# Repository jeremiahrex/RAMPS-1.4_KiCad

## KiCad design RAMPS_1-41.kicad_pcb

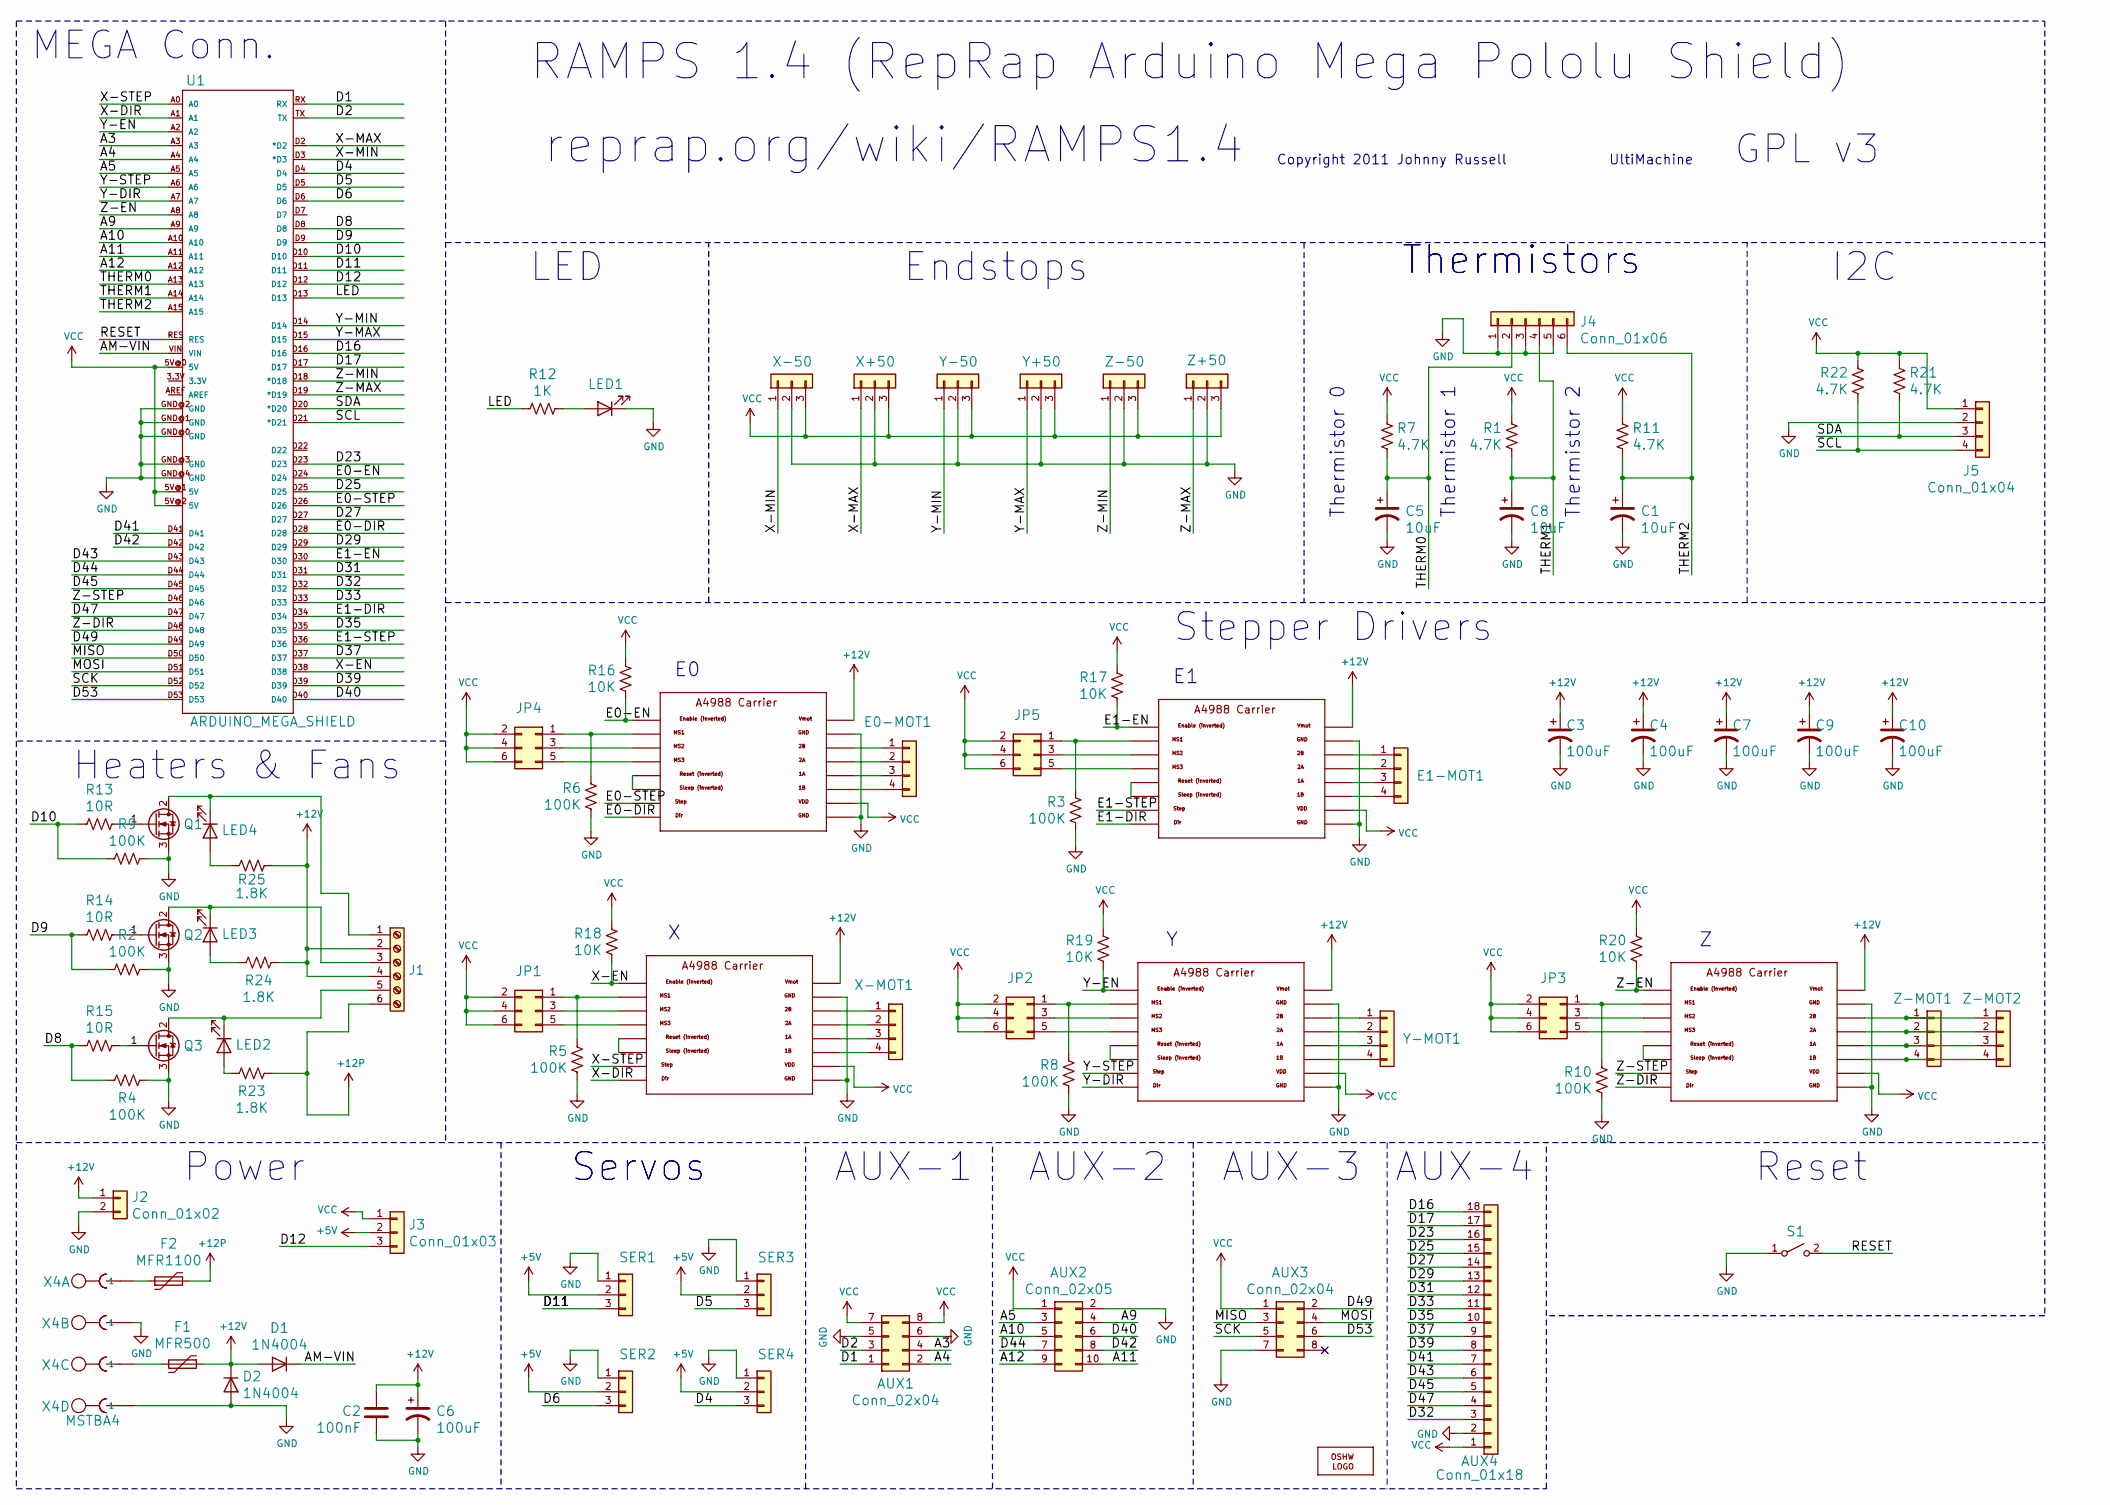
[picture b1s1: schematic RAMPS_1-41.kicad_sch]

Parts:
AUX1, AUX3: Conn_02x04; PIN-HEADER-2x04
AUX2: Conn_02x05; PIN-HEADER-2x05
AUX4: Conn_01x18; PIN-HEADER-1x18
C1, C5, C8: 10uF; CP_Elec_4x5.3
C2: 100nF; C_0805_2012Metric
C3, C4, C6, C7, C9, C10: 100uF; CP_Elec_6.3x5.4
D1, D2: 1N4004; D_DO-41_SOD81_P10.16mm_Horizontal
E0-MOT1, E1-MOT1: PIN-HEADER-1x04
F1: MFR500
F2: MFR1100
J1: 282837-6; TerminalBlock_MetzConnect_Type101_RT01606HBWC_1x06_P5.08mm_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
J2: Conn_01x02; PIN-HEADER-1x02
J3: Conn_01x03; PIN-HEADER-1x03
J4: Conn_01x06; PIN-HEADER-1x06
J5: Conn_01x04; PIN-HEADER-1x04
JP1, JP2, JP3, JP4, JP5: PIN-HEADER-2x03
LED1, LED2, LED3, LED4: LED_0805
LOGO1: OSHW_LOGO_6MILX0100-NT; OSHW_OSHW_6X100_NOTEXT
Q1, Q2, Q3: STP55NF06L; TRANSISTOR-POWER_TO220BV
R1, R7, R11, R21, R22: 4.7K; R_0805_2012Metric
R2, R3, R4, R5, R6, R8, R9, R10: 100K; R_0805_2012Metric
R12: 1K; R_0805_2012Metric
R13, R14, R15: 10R; R_0805_2012Metric
R16, R17, R18, R19, R20: 10K; R_0805_2012Metric
R23, R24, R25: 1.8K; R_0805_2012Metric
S1: SWITCH-OMRON_B3F-31XX
SER1, SER2, SER3, SER4: Conn_01x03; PIN-HEADER-1x03
U1: ARDUINO_MEGA_SHIELD
U2, U3, U4, U5, U6: A4988BREAKOUT; A4988_BREAKOUT
X4: MSTBA4; PhoenixContact_MSTBA_2,5_4-G-5,08_1x04_P5.08mm_Horizontal
X+50: PIN-HEADER-1x03
X-50: PIN-HEADER-1x03
X-MOT1: PIN-HEADER-1x04
Y+50: PIN-HEADER-1x03
Y-50: PIN-HEADER-1x03
Y-MOT1: PIN-HEADER-1x04
Z+50: PIN-HEADER-1x03
Z-50: PIN-HEADER-1x03
Z-MOT1, Z-MOT2: PIN-HEADER-1x04

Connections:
+5V: J3.2, SER1.2, SER2.2, SER3.2, SER4.2
+12P: F2.2, J1.6, R23.2
+12V: C2.1, C3.1, C4.1, C6.1, C7.1, C9.1, C10.1, D1.2 (A), D2.1 (K), F1.1, J1.2, J1.4, J2.1, R24.2, R25.2, U2.VMOT, U3.VMOT, U4.VMOT, U5.VMOT, U6.VMOT
/A3: AUX1.4, U1.A3
/A4: AUX1.2, U1.A4
/A5: AUX2.3, U1.A5
/A9: AUX2.4, U1.A9
/A10: AUX2.5, U1.A10
/A11: AUX2.10, U1.A11
/A12: AUX2.9, U1.A12
/AM-VIN: D1.1 (K), U1.VIN
/D1: AUX1.1, U1.RX
/D2: AUX1.3, U1.TX
/D4: SER4.3, U1.D4
/D5: SER3.3, U1.D5
/D6: SER2.3, U1.D6
/D8: R4.2, R15.2, U1.D8
/D9: R2.2, R14.2, U1.D9
/D10: R9.2, R13.2, U1.D10
/D11: SER1.3, U1.D11
/D12: J3.3, U1.D12
/D16: AUX4.18, U1.D16
/D17: AUX4.17, U1.D17
/D23: AUX4.16, U1.D23
/D25: AUX4.15, U1.D25
/D27: AUX4.14, U1.D27
/D29: AUX4.13, U1.D29
/D31: AUX4.12, U1.D31
/D32: AUX4.3, U1.D32
/D33: AUX4.11, U1.D33
/D35: AUX4.10, U1.D35
/D37: AUX4.9, U1.D37
/D39: AUX4.8, U1.D39
/D40: AUX2.6, U1.D40
/D41: AUX4.7, U1.D41
/D42: AUX2.8, U1.D42
/D43: AUX4.6, U1.D43
/D44: AUX2.7, U1.D44
/D45: AUX4.5, U1.D45
/D47: AUX4.4, U1.D47
/D49: AUX3.2, U1.D49
/D53: AUX3.6, U1.D53
/E0-DIR: U1.D28, U5.DIR
/E0-EN: R16.1, U1.D24, U5.EN
/E0-STEP: U1.D26, U5.STEP
/E1-DIR: U1.D34, U6.DIR
/E1-EN: R17.1, U1.D30, U6.EN
/E1-STEP: U1.D36, U6.STEP
/LED: R12.1, U1.D13
/MISO: AUX3.3, U1.D50
/MOSI: AUX3.4, U1.D51
/RESET: S1.2 (B), U1.RES
/SCK: AUX3.5, U1.D52
/SCL: J5.4, R22.2, U1.D21 (*D21)
/SDA: J5.3, R21.2, U1.D20 (*D20)
/THERM0: C5.1, J4.2, R7.2, U1.A13
/THERM1: C8.1, J4.4, R1.2, U1.A14
/THERM2: C1.1, J4.6, R11.2, U1.A15
/X-DIR: U1.A1, U2.DIR
/X-EN: R18.1, U1.D38, U2.EN
/X-MAX: U1.D2 (*D2), X+50.1
/X-MIN: U1.D3 (*D3), X-50.1
/X-STEP: U1.A0, U2.STEP
/Y-DIR: U1.A7, U3.DIR
/Y-EN: R19.1, U1.A2, U3.EN
/Y-MAX: U1.D15, Y+50.1
/Y-MIN: U1.D14, Y-50.1
/Y-STEP: U1.A6, U3.STEP
/Z-DIR: U1.D48, U4.DIR
/Z-EN: R20.1, U1.A8, U4.EN
/Z-MAX: U1.D19 (*D19), Z+50.1
/Z-MIN: U1.D18 (*D18), Z-50.1
/Z-STEP: U1.D46, U4.STEP
GND: AUX1.5, AUX1.6, AUX2.2, AUX3.7, AUX4.2, C1.2, C2.2, C3.2, C4.2, C5.2, C6.2, C7.2, C8.2, C9.2, C10.2, D2.2 (A), J2.2, J4.1, J4.3, J4.5, J5.2, LED1.1 (K), Q1.3 (S), Q2.3 (S), Q3.3 (S), R2.1, R3.1, R4.1, R5.1, R6.2, R8.1, R9.1, R10.1, S1.1 (A), SER1.1, SER2.1, SER3.1, SER4.1, U1.GND@0 (GND), U1.GND@1 (GND), U1.GND@2 (GND), U1.GND@3 (GND), U1.GND@4 (GND), U2.GND, U2.GND@0 (GND), U3.GND, U3.GND@0 (GND), U4.GND, U4.GND@0 (GND), U5.GND, U5.GND@0 (GND), U6.GND, U6.GND@0 (GND), X4.2 (1), X4.4 (1), X+50.2, X-50.2, Y+50.2, Y-50.2, Z+50.2, Z-50.2
unnamed: E0-MOT1.1, U5.2B
unnamed: E0-MOT1.2, U5.2A
unnamed: E0-MOT1.3, U5.1A
unnamed: E0-MOT1.4, U5.1B
unnamed: E1-MOT1.1, U6.2B
unnamed: E1-MOT1.2, U6.2A
unnamed: E1-MOT1.3, U6.1A
unnamed: E1-MOT1.4, U6.1B
unnamed: F2.1, X4.1
unnamed: J1.1, LED4.1 (K), Q1.2 (D)
unnamed: J1.3, LED3.1 (K), Q2.2 (D)
unnamed: J1.5, LED2.1 (K), Q3.2 (D)
unnamed: JP1.1, R5.2, U2.MS1
unnamed: JP1.3, U2.MS2
unnamed: JP1.5, U2.MS3
unnamed: JP2.1, R8.2, U3.MS1
unnamed: JP2.3, U3.MS2
unnamed: JP2.5, U3.MS3
unnamed: JP3.1, R10.2, U4.MS1
unnamed: JP3.3, U4.MS2
unnamed: JP3.5, U4.MS3
unnamed: JP4.1, R6.1, U5.MS1
unnamed: JP4.3, U5.MS2
unnamed: JP4.5, U5.MS3
unnamed: JP5.1, R3.2, U6.MS1
unnamed: JP5.3, U6.MS2
unnamed: JP5.5, U6.MS3
unnamed: LED1.2 (A), R12.2
unnamed: LED2.2 (A), R23.1
unnamed: LED3.2 (A), R24.1
unnamed: LED4.2 (A), R25.1
unnamed: Q1.1 (G), R13.1
unnamed: Q2.1 (G), R14.1
unnamed: Q3.1 (G), R15.1
unnamed: U2.RST, U2.SLP (SLEEP)
unnamed: U3.RST, U3.SLP (SLEEP)
unnamed: U4.RST, U4.SLP (SLEEP)
unnamed: U5.RST, U5.SLP (SLEEP)
unnamed: U6.RST, U6.SLP (SLEEP)
unnamed: F1.2, X4.3 (1)
unnamed: U2.2B, X-MOT1.1
unnamed: U2.2A, X-MOT1.2
unnamed: U2.1A, X-MOT1.3
unnamed: U2.1B, X-MOT1.4
unnamed: U3.2B, Y-MOT1.1
unnamed: U3.2A, Y-MOT1.2
unnamed: U3.1A, Y-MOT1.3
unnamed: U3.1B, Y-MOT1.4
unnamed: U4.2B, Z-MOT1.1, Z-MOT2.1
unnamed: U4.2A, Z-MOT1.2, Z-MOT2.2
unnamed: U4.1A, Z-MOT1.3, Z-MOT2.3
unnamed: U4.1B, Z-MOT1.4, Z-MOT2.4
VCC: AUX1.7, AUX1.8, AUX2.1, AUX3.1, AUX4.1, J3.1, J5.1, JP1.2, JP1.4, JP1.6, JP2.2, JP2.4, JP2.6, JP3.2, JP3.4, JP3.6, JP4.2, JP4.4, JP4.6, JP5.2, JP5.4, JP5.6, R1.1, R7.1, R11.1, R16.2, R17.2, R18.2, R19.2, R20.2, R21.1, R22.1, U1.5V@0 (5V), U1.5V@1 (5V), U1.5V@2 (5V), U2.VDD, U3.VDD, U4.VDD, U5.VDD, U6.VDD, X+50.3, X-50.3, Y+50.3, Y-50.3, Z+50.3, Z-50.3

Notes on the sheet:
Copyright 2011 Johnny Russell
Power
Endstops
MEGA Conn.
AUX-3
reprap.org/wiki/RAMPS1.4
AUX-1
Thermistor 2
Servos
Thermistors
Reset
Thermistor 0
Stepper Drivers
Thermistor 1
LED
GPL v3
AUX-2
RAMPS 1.4 (RepRap Arduino Mega Pololu Shield)
AUX-4
UltiMachine
Heaters & Fans
I2C

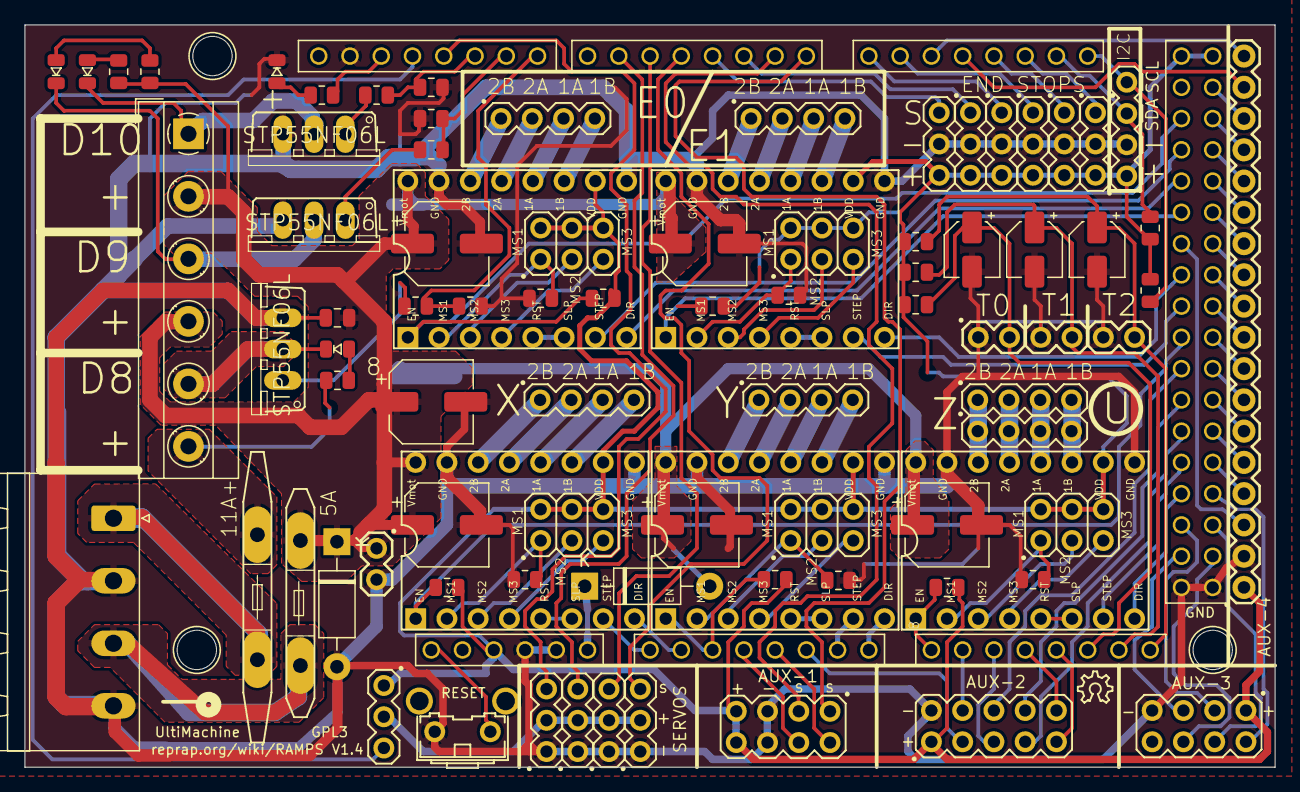
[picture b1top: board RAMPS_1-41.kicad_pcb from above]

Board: 2 copper layers, 101.6 x 60.3 mm, 85 parts (0 on the bottom side), 127 nets.

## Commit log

2024-06-01 Kicad 8 project files
    Remove old .pro and add new kicad_pro, fix the gitignore.
2024-06-01 Kicad 8 updates
    Remove unused files
    Update schematic and PCB files to Kicad 8 format
    "Rescue" some symbols
2024-06-01 Update symbols
    Updated all the rescue symbols and deleted the cache files
2024-06-01 Tweak that gitignore one more time
2024-06-02 Cleanup of imported PCB
    Fix traces with insufficient clearance
    Removed unused markings from User.Drawings and User.Eco1
    Tidy up silkscreen and add a few additional markings
2024-07-20 TMC updates
    Added closed solder jumpers to ~Reset and ~Sleep to make it easier to use Trinamic SPI drivers.
    Updated A4988 symbol to Trinamic SPI pin names in parathesis.
2024-07-20 Delete RAMPS_1-41.lib
    Removed .lib file, migrated this lib to new KiCad format in previous commit.
2024-07-20 Update RAMPS_1-41.kicad_sch
    Apparently I didn't update the A4988 schematic symbols after I changed the lib

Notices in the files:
RAMPS_1-41.kicad_pcb:
GPL3
Copyright 2011 Johnny Russell - UltiMachine
